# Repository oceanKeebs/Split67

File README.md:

# Split67

Split67 is a splitted common 67% ISO DE keyboard layout with processor daughterboards extended by a side case housing a TPS43 touch pad and a 64x128 Oled display. Left and right keyboard Pcb is connected with TRRS using serial communication, right keyboard part and sidecase are connected with TRRS using i2c communication. To support a close contact of the parts, magnets are used.

## QMK Firmware source files

<https://github.com/oceanKeebs/qmk_firmware/tree/master/keyboards/oceankeebs/split67>

## QMK Firmware hex files

**without via support:**
[Split67_defaultHex](HexFiles/oceankeebs_split67_default.hex)

**with via support:**
[Split67_viaHex](HexFiles/oceankeebs_split67_via.hex)

## PCBs

### Processor Board

The processor board includes the ProMicro and connectors for i2c, serial communication and keyboard Pcb control.

### Left Pcb

### Right Pcb

## Case

### Left keyboard part

[LeftCaseTop_stl](StlFiles/Case_L_B.stl)

[LeftCaseBottom_stl](StlFiles/Bottom_L.stl)

### Right keyboard part

[RightCaseTop_stl](StlFiles/Case_R_B.stl)

[RightCaseBottom_stl](StlFiles/Bottom_R.stl)

[UsbCoverBase_stl](StlFiles/USB-Cover_Base.stl)

[UsbCoverTop_stl](StlFiles/USB-Cover_Top.stl)

### SideCase

[SideCaseTop_stl](StlFiles/SideCase_B.stl)

[SideCaseBottom_stl](StlFiles/Bottom_Sidecase.stl)

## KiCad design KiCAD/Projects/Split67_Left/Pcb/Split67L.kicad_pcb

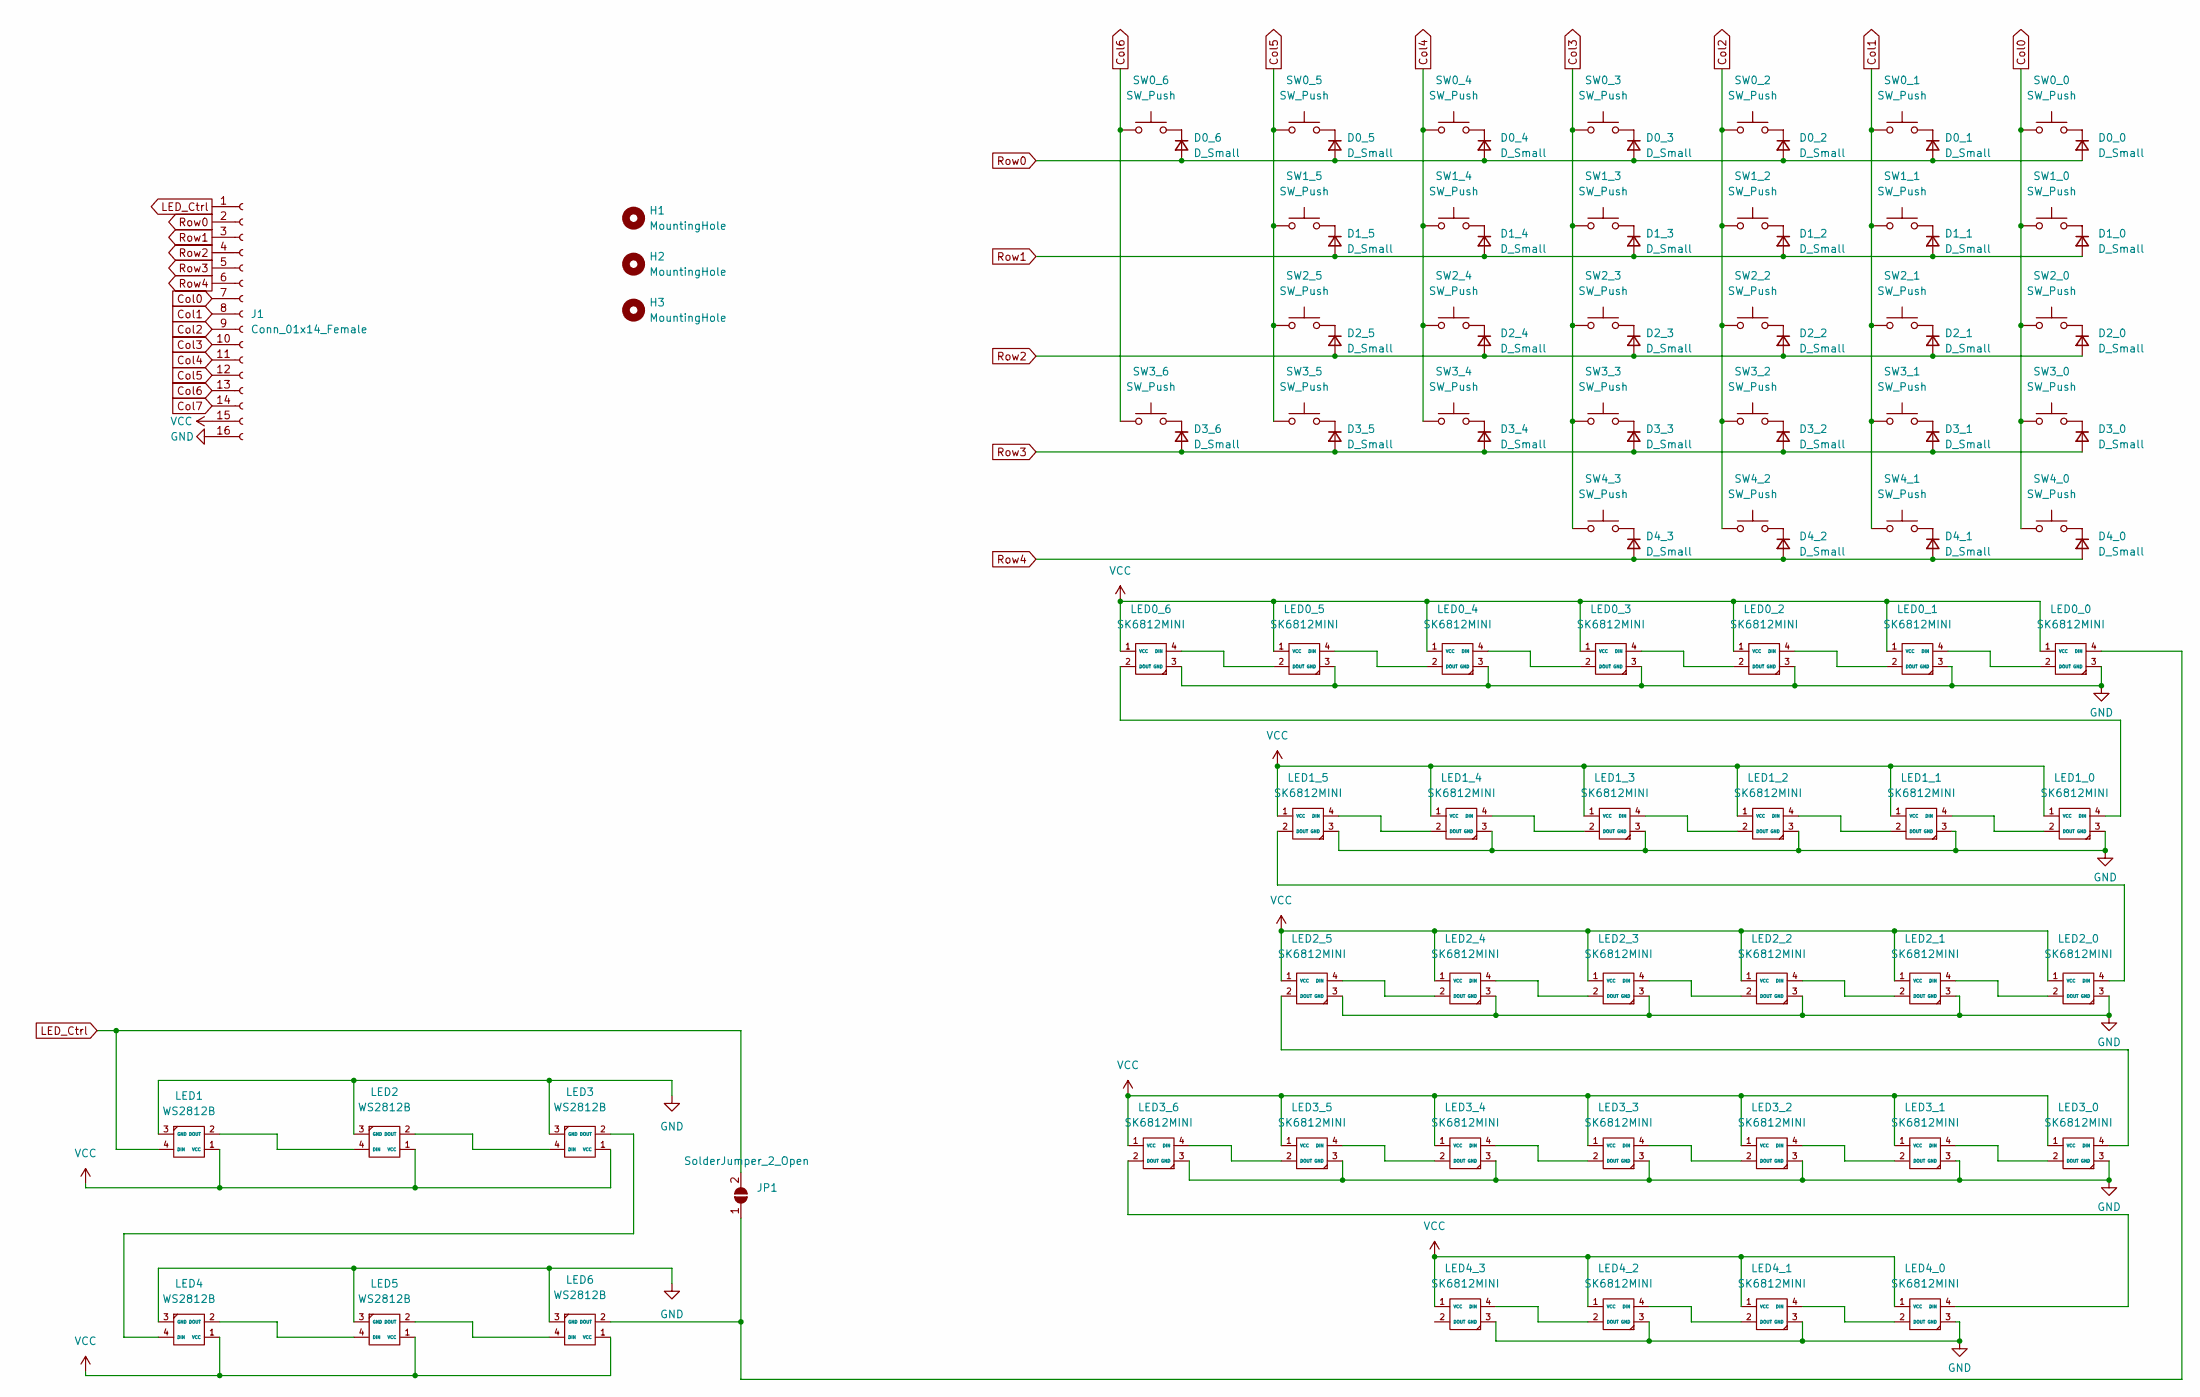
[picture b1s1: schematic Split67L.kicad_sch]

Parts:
D0_0, D0_1, D0_2, D0_3, D0_4, D0_5, D0_6, D1_0, D1_1, D1_2, D1_3, D1_4, D1_5, D2_0, D2_1, D2_2, D2_3, D2_4, D2_5, D3_0, D3_1, D3_2, D3_3, D3_4, D3_5, D3_6, D4_0, D4_1, D4_2, D4_3: D_Small; Diode_SMD_Round_Pads
H1, H2, H3: MountingHole; MountingHole_2.2mm_M2
J1: Conn_01x14_Female; PinHeader_1x16_P2.54mm_Vertical
JP1: SolderJumper_2_Open; SolderJumper-2_P1.3mm_Open_RoundedPad1.0x1.5mm
LED0_0, LED0_1, LED0_2, LED0_3, LED0_4, LED0_5, LED0_6, LED1_0, LED1_1, LED1_2, LED1_3, LED1_4, LED1_5, LED2_0, LED2_1, LED2_2, LED2_3, LED2_4, LED2_5, LED3_0, LED3_1, LED3_2, LED3_3, LED3_4, LED3_5, LED3_6, LED4_0, LED4_1, LED4_2, LED4_3: SK6812MINI; SK6812MiniE_MX_Addon_singlesided
LED1, LED2, LED3, LED4, LED5, LED6: WS2812B
SW0_0, SW0_1, SW0_2, SW0_3, SW0_4, SW0_5, SW0_6, SW1_1, SW1_2, SW1_3, SW1_4, SW1_5, SW2_1, SW2_2, SW2_3, SW2_4, SW2_5, SW3_1, SW3_2, SW3_3, SW3_4, SW3_5, SW3_6: SW_Push; MX_lss_100U
SW1_0: SW_Push; MX_lss_150U
SW2_0: SW_Push; MX_lss_175U
SW3_0, SW4_0, SW4_1, SW4_2: SW_Push; MX_lss_125U
SW4_3: SW_Push; MX_lss_275U_StWN

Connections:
Col0: J1.7, SW0_0.1, SW1_0.1, SW2_0.1, SW3_0.1, SW4_0.1
Col1: J1.8, SW0_1.1, SW1_1.1, SW2_1.1, SW3_1.1, SW4_1.1
Col2: J1.9, SW0_2.1, SW1_2.1, SW2_2.1, SW3_2.1, SW4_2.1
Col3: J1.10, SW0_3.1, SW1_3.1, SW2_3.1, SW3_3.1, SW4_3.1
Col4: J1.11, SW0_4.1, SW1_4.1, SW2_4.1, SW3_4.1
Col5: J1.12, SW0_5.1, SW1_5.1, SW2_5.1, SW3_5.1
Col6: J1.13, SW0_6.1, SW3_6.1
Col7: J1.14
GND: J1.16, LED0_0.3 (GND), LED0_1.3 (GND), LED0_2.3 (GND), LED0_3.3 (GND), LED0_4.3 (GND), LED0_5.3 (GND), LED0_6.3 (GND), LED1.3 (GND), LED1_0.3 (GND), LED1_1.3 (GND), LED1_2.3 (GND), LED1_3.3 (GND), LED1_4.3 (GND), LED1_5.3 (GND), LED2.3 (GND), LED2_0.3 (GND), LED2_1.3 (GND), LED2_2.3 (GND), LED2_3.3 (GND), LED2_4.3 (GND), LED2_5.3 (GND), LED3.3 (GND), LED3_0.3 (GND), LED3_1.3 (GND), LED3_2.3 (GND), LED3_3.3 (GND), LED3_4.3 (GND), LED3_5.3 (GND), LED3_6.3 (GND), LED4.3 (GND), LED4_0.3 (GND), LED4_1.3 (GND), LED4_2.3 (GND), LED4_3.3 (GND), LED5.3 (GND), LED6.3 (GND)
LED_Ctrl: J1.1, JP1.2 (B), LED1.4 (DIN)
unnamed: D0_0.1 (K), SW0_0.2
unnamed: D0_1.1 (K), SW0_1.2
unnamed: D0_2.1 (K), SW0_2.2
unnamed: D0_3.1 (K), SW0_3.2
unnamed: D0_4.1 (K), SW0_4.2
unnamed: D0_5.1 (K), SW0_5.2
unnamed: D1_0.1 (K), SW1_0.2
unnamed: D1_1.1 (K), SW1_1.2
unnamed: D1_2.1 (K), SW1_2.2
unnamed: D1_3.1 (K), SW1_3.2
unnamed: D1_4.1 (K), SW1_4.2
unnamed: D1_5.1 (K), SW1_5.2
unnamed: D2_0.1 (K), SW2_0.2
unnamed: D2_1.1 (K), SW2_1.2
unnamed: D2_2.1 (K), SW2_2.2
unnamed: D2_3.1 (K), SW2_3.2
unnamed: D2_4.1 (K), SW2_4.2
unnamed: D2_5.1 (K), SW2_5.2
unnamed: D3_0.1 (K), SW3_0.2
unnamed: D3_1.1 (K), SW3_1.2
unnamed: D3_2.1 (K), SW3_2.2
unnamed: D3_3.1 (K), SW3_3.2
unnamed: D3_4.1 (K), SW3_4.2
unnamed: D3_5.1 (K), SW3_5.2
unnamed: D4_0.1 (K), SW4_0.2
unnamed: D4_1.1 (K), SW4_1.2
unnamed: D4_2.1 (K), SW4_2.2
unnamed: JP1.1 (A), LED0_0.4 (DIN), LED6.2 (DOUT)
unnamed: LED0_0.2 (DOUT), LED0_1.4 (DIN)
unnamed: LED0_1.2 (DOUT), LED0_2.4 (DIN)
unnamed: LED0_2.2 (DOUT), LED0_3.4 (DIN)
unnamed: LED0_3.2 (DOUT), LED0_4.4 (DIN)
unnamed: LED0_4.2 (DOUT), LED0_5.4 (DIN)
unnamed: LED0_5.2 (DOUT), LED0_6.4 (DIN)
unnamed: LED1.2 (DOUT), LED2.4 (DIN)
unnamed: LED1_0.2 (DOUT), LED1_1.4 (DIN)
unnamed: LED0_6.2 (DOUT), LED1_0.4 (DIN)
unnamed: LED1_1.2 (DOUT), LED1_2.4 (DIN)
unnamed: LED1_2.2 (DOUT), LED1_3.4 (DIN)
unnamed: LED1_3.2 (DOUT), LED1_4.4 (DIN)
unnamed: LED1_4.2 (DOUT), LED1_5.4 (DIN)
unnamed: LED2.2 (DOUT), LED3.4 (DIN)
unnamed: LED2_0.2 (DOUT), LED2_1.4 (DIN)
unnamed: LED1_5.2 (DOUT), LED2_0.4 (DIN)
unnamed: LED2_1.2 (DOUT), LED2_2.4 (DIN)
unnamed: LED2_2.2 (DOUT), LED2_3.4 (DIN)
unnamed: LED2_3.2 (DOUT), LED2_4.4 (DIN)
unnamed: LED2_4.2 (DOUT), LED2_5.4 (DIN)
unnamed: LED3.2 (DOUT), LED4.4 (DIN)
unnamed: LED3_0.2 (DOUT), LED3_1.4 (DIN)
unnamed: LED2_5.2 (DOUT), LED3_0.4 (DIN)
unnamed: LED3_1.2 (DOUT), LED3_2.4 (DIN)
unnamed: LED3_2.2 (DOUT), LED3_3.4 (DIN)
unnamed: LED3_3.2 (DOUT), LED3_4.4 (DIN)
unnamed: LED3_4.2 (DOUT), LED3_5.4 (DIN)
unnamed: LED3_5.2 (DOUT), LED3_6.4 (DIN)
unnamed: LED4.2 (DOUT), LED5.4 (DIN)
unnamed: LED4_0.2 (DOUT), LED4_1.4 (DIN)
unnamed: LED3_6.2 (DOUT), LED4_0.4 (DIN)
unnamed: LED4_1.2 (DOUT), LED4_2.4 (DIN)
unnamed: LED4_2.2 (DOUT), LED4_3.4 (DIN)
unnamed: LED5.2 (DOUT), LED6.4 (DIN)
unnamed: D0_6.1 (K), SW0_6.2
unnamed: D3_6.1 (K), SW3_6.2
unnamed: D4_3.1 (K), SW4_3.2
Row0: D0_0.2 (A), D0_1.2 (A), D0_2.2 (A), D0_3.2 (A), D0_4.2 (A), D0_5.2 (A), D0_6.2 (A), J1.2
Row1: D1_0.2 (A), D1_1.2 (A), D1_2.2 (A), D1_3.2 (A), D1_4.2 (A), D1_5.2 (A), J1.3
Row2: D2_0.2 (A), D2_1.2 (A), D2_2.2 (A), D2_3.2 (A), D2_4.2 (A), D2_5.2 (A), J1.4
Row3: D3_0.2 (A), D3_1.2 (A), D3_2.2 (A), D3_3.2 (A), D3_4.2 (A), D3_5.2 (A), D3_6.2 (A), J1.5
Row4: D4_0.2 (A), D4_1.2 (A), D4_2.2 (A), D4_3.2 (A), J1.6
VCC: J1.15, LED0_0.1 (VCC), LED0_1.1 (VCC), LED0_2.1 (VCC), LED0_3.1 (VCC), LED0_4.1 (VCC), LED0_5.1 (VCC), LED0_6.1 (VCC), LED1.1 (VCC), LED1_0.1 (VCC), LED1_1.1 (VCC), LED1_2.1 (VCC), LED1_3.1 (VCC), LED1_4.1 (VCC), LED1_5.1 (VCC), LED2.1 (VCC), LED2_0.1 (VCC), LED2_1.1 (VCC), LED2_2.1 (VCC), LED2_3.1 (VCC), LED2_4.1 (VCC), LED2_5.1 (VCC), LED3.1 (VCC), LED3_0.1 (VCC), LED3_1.1 (VCC), LED3_2.1 (VCC), LED3_3.1 (VCC), LED3_4.1 (VCC), LED3_5.1 (VCC), LED3_6.1 (VCC), LED4.1 (VCC), LED4_0.1 (VCC), LED4_1.1 (VCC), LED4_2.1 (VCC), LED4_3.1 (VCC), LED5.1 (VCC), LED6.1 (VCC)

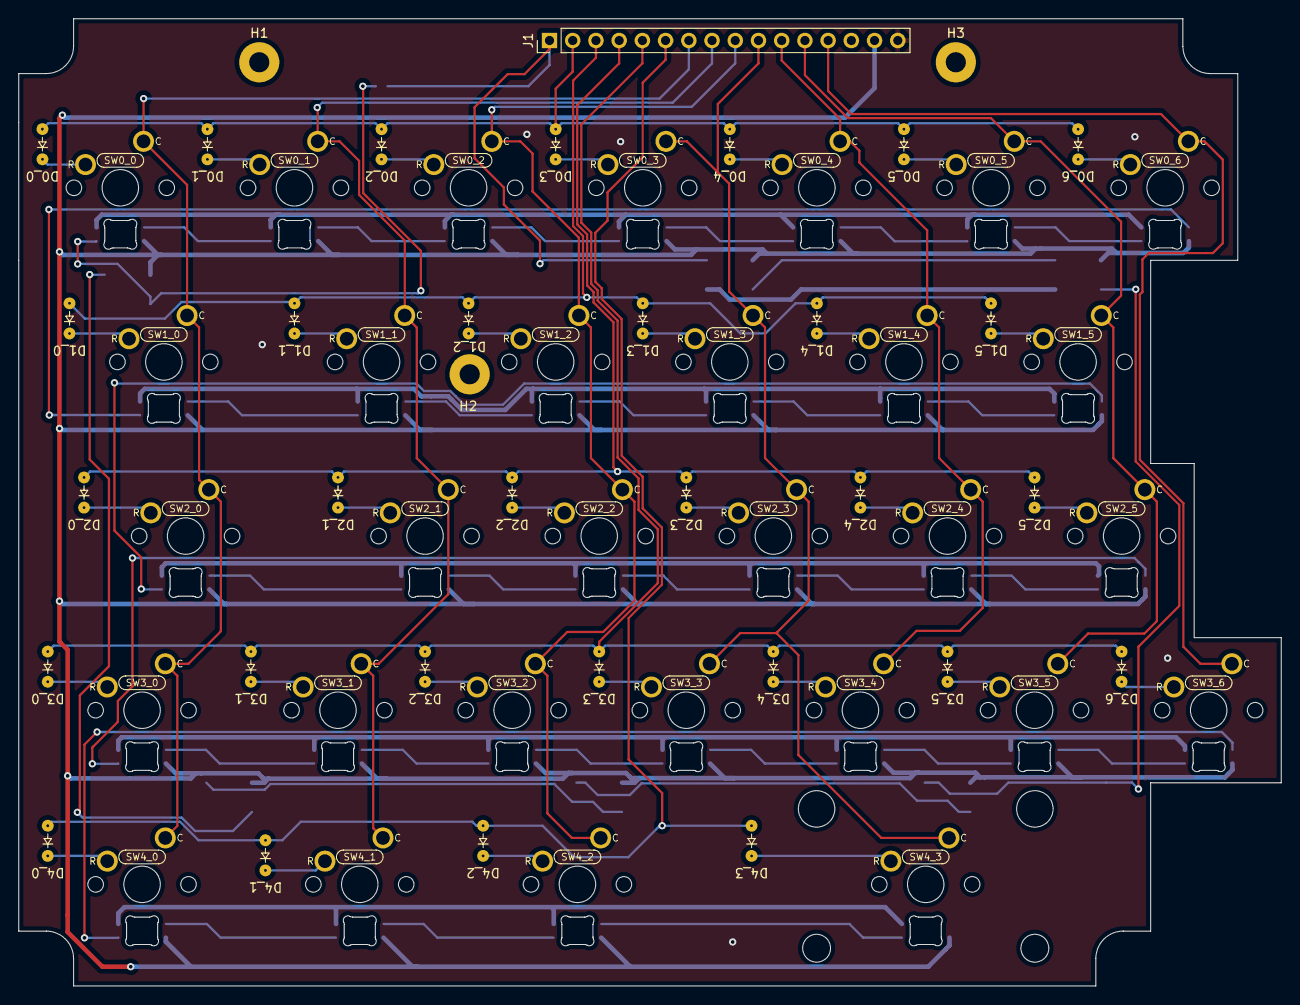
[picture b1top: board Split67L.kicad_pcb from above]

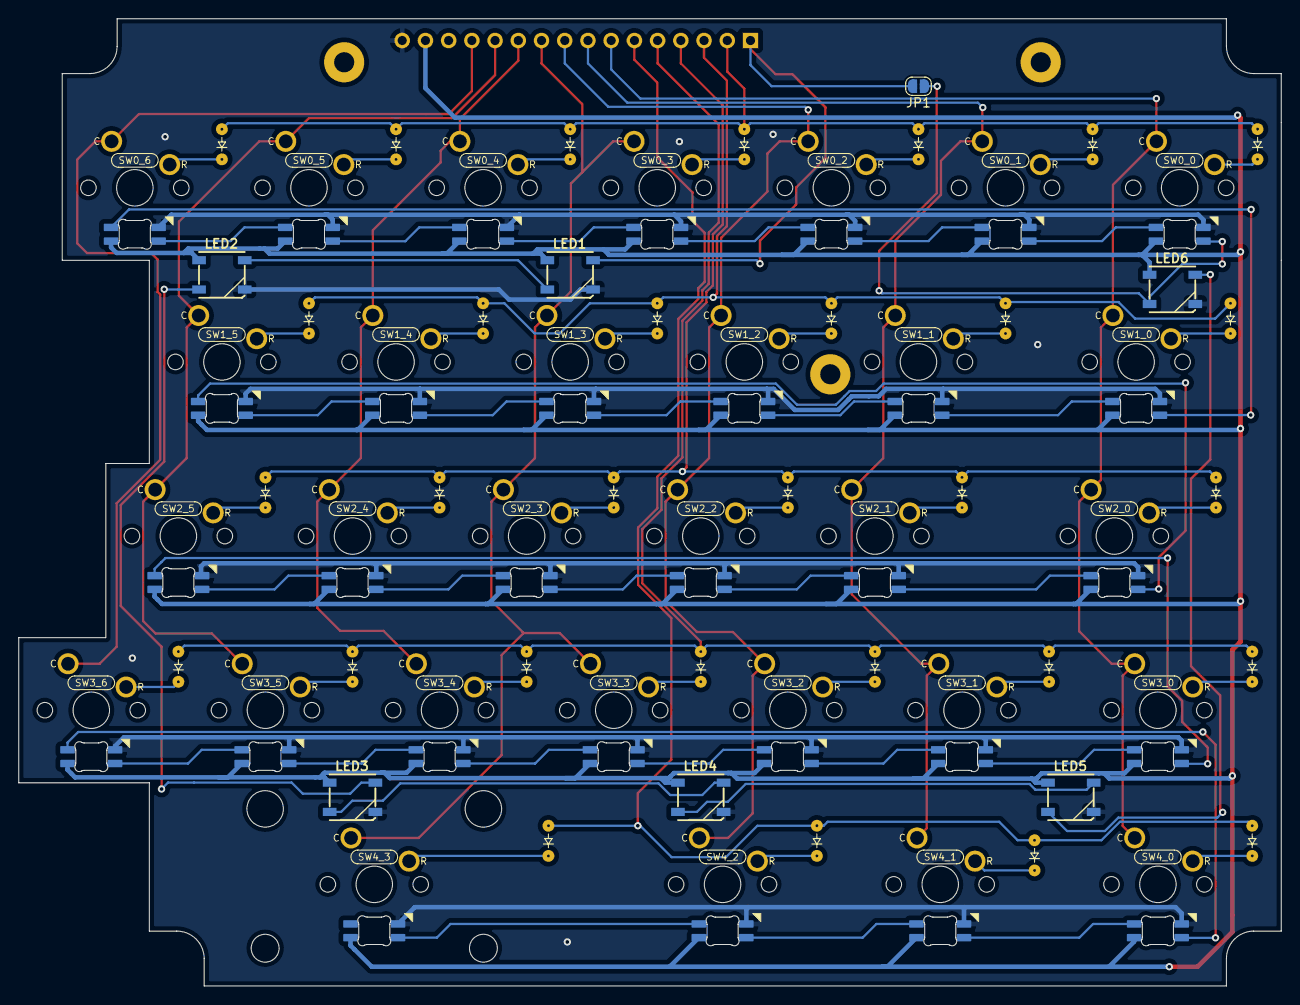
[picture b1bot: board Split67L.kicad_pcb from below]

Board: 2 copper layers, 138.1 x 105.8 mm, 101 parts (7 on the bottom side), 80 nets.

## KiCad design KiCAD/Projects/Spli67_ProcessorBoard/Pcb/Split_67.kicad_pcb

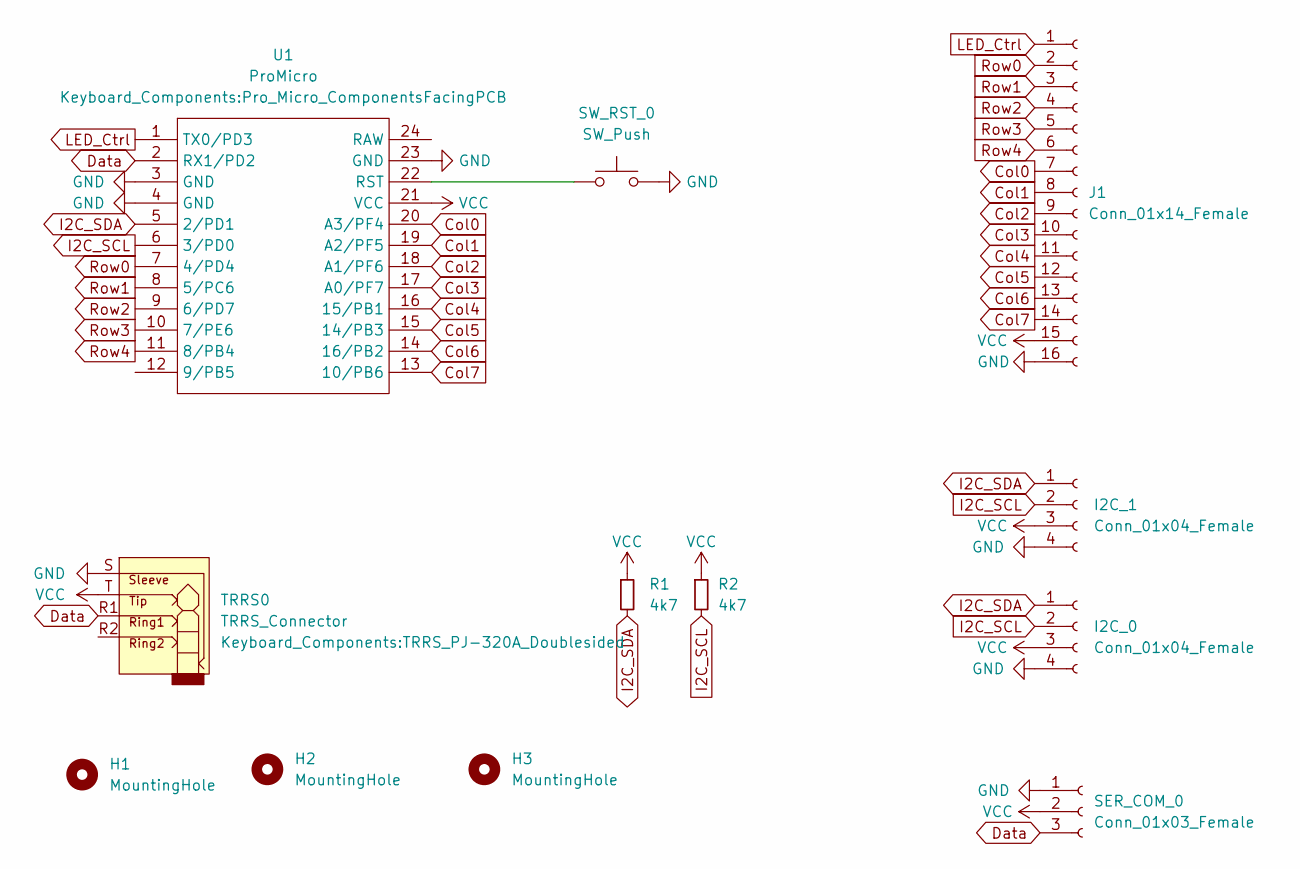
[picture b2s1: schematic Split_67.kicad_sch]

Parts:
H1, H2, H3: MountingHole; M2_Mountinghole
I2C_0, I2C_1: Conn_01x04_Female; PinHeader_1x04_P2.54mm_Vertical
J1: Conn_01x14_Female; PinHeader_1x16_P2.54mm_Vertical
R1, R2: 4k7; Resistor
SER_COM_0: Conn_01x03_Female; PinHeader_1x03_P2.54mm_Vertical
SW_RST_0: SW_Push; Reset_Switch
TRRS0: TRRS_Connector; TRRS_PJ-320A_Doublesided
U1: ProMicro; Pro_Micro_ComponentsFacingPCB

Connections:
Col0: J1.7, U1.20 (A3/PF4)
Col1: J1.8, U1.19 (A2/PF5)
Col2: J1.9, U1.18 (A1/PF6)
Col3: J1.10, U1.17 (A0/PF7)
Col4: J1.11, U1.16 (15/PB1)
Col5: J1.12, U1.15 (14/PB3)
Col6: J1.13, U1.14 (16/PB2)
Col7: J1.14, U1.13 (10/PB6)
Data: SER_COM_0.3, TRRS0.R1, U1.2 (RX1/PD2)
GND: I2C_0.4, I2C_1.4, J1.16, SER_COM_0.1, SW_RST_0.2, TRRS0.S, U1.3 (GND), U1.4 (GND), U1.23 (GND)
I2C_SCL: I2C_0.2, I2C_1.2, R2.2, U1.6 (3/PD0)
I2C_SDA: I2C_0.1, I2C_1.1, R1.2, U1.5 (2/PD1)
LED_Ctrl: J1.1, U1.1 (TX0/PD3)
unnamed: SW_RST_0.1, U1.22 (RST)
Row0: J1.2, U1.7 (4/PD4)
Row1: J1.3, U1.8 (5/PC6)
Row2: J1.4, U1.9 (6/PD7)
Row3: J1.5, U1.10 (7/PE6)
Row4: J1.6, U1.11 (8/PB4)
VCC: I2C_0.3, I2C_1.3, J1.15, R1.1, R2.1, SER_COM_0.2, TRRS0.T, U1.21 (VCC)

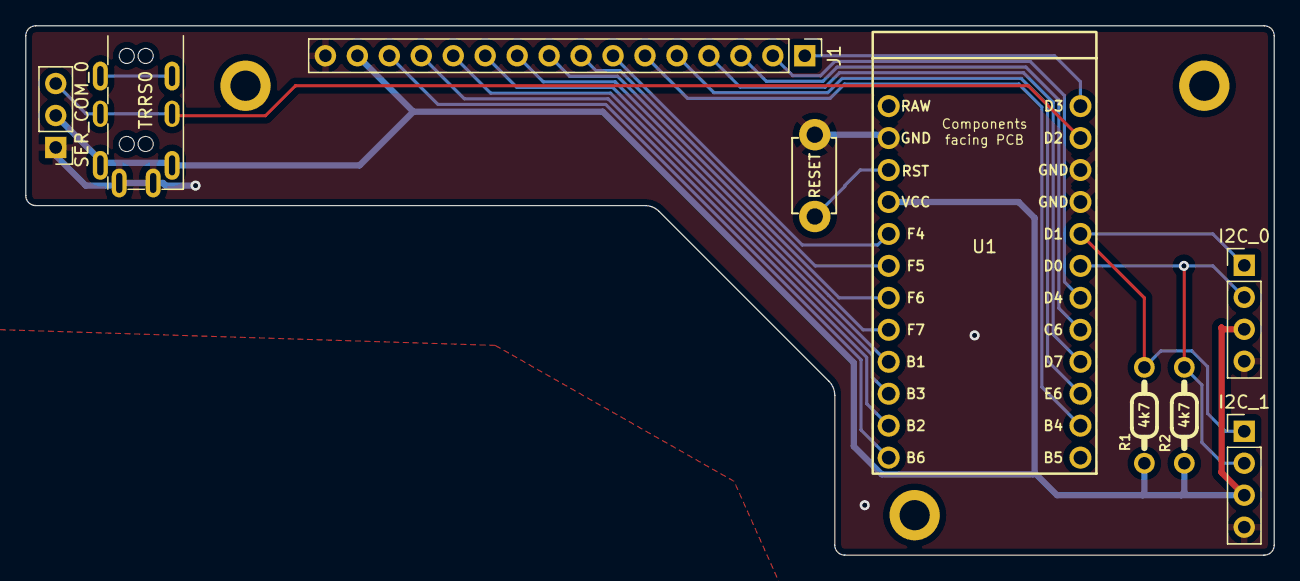
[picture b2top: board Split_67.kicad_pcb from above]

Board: 2 copper layers, 99.2 x 42.1 mm, 12 parts (0 on the bottom side), 20 nets.

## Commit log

2024-04-03 Split67 info added
